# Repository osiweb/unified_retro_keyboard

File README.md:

## Unified Retrocomputer Keyboard Project

This project aims to provide a unified collection of keyboards and encoders for
vintage computers, with modular design to reuse as many elements as possible
across the designs.

Home computers of the 1970's typically either polled a switch matrix, or
interfaced to a parallel ASCII keyboard via a parallel port.

The keyboard allows use of Cherry MX keys, or Futaba MD-4PCS (aka George Risk
KBM-01-01) keys.

The keyboard is designed using KiCad in order to be the most useful for anybody
wishing to modify the keyboard for more specific uses, or to add to the project.

For construction and notes, see the the wiki at https://github.com/osiweb/unified_retro_keyboard/wiki.

### Capabilities so far:
- Replacement keyboard for OSI computers
- Replacement keyboard for Apple II/II+ computers
- Replacement keyboard for the Sol-20 computer
- Generic ADM-3A/Teletype style keyboard
- Apple I keyboard (multiple styles)
- Franklin ACE 1000 replacement keyboard by Chris Ryu (https://github.com/ryucats/Franklin-ACE-1000-Keyboard)

### Coming soon:
- Replace encoder board on Apple II/II+ keyboards
- Convert an OSI 542 keyboard into a generic ASCII keyboard
- Replica for Knight keyboard

### This keyboard project so far consists of:
- A classic retro-style ASCII keyboard, modeled after the ADM-3A keyboard, which
  can be also be populated to fit perfectly in an Apple II/II+ case (with corresponding Apple II keymaps), or an OSI
  case (with OSI adapter).
- A Sol-20 compatible keyboard.
- Keyscan/decoder interface modules that can output parallel ASCII, and can be adapted for other protocols.
- An OSI interface module, to connect the classic keyboard to an OSI computer.

### Firmware

The ASDF keyscan/encoder firmware lives in its own repository:
<https://github.com/unified-retro-keyboard/asdf-firmware>

- **Download page**: <https://unified-retro-keyboard.github.io/asdf-firmware/> — per-target `.hex` files and release notes.
- **GitHub Releases**: <https://github.com/unified-retro-keyboard/asdf-firmware/releases/latest>

The full firmware history, including everything that was previously under `firmware/`
in this repository, is preserved there.

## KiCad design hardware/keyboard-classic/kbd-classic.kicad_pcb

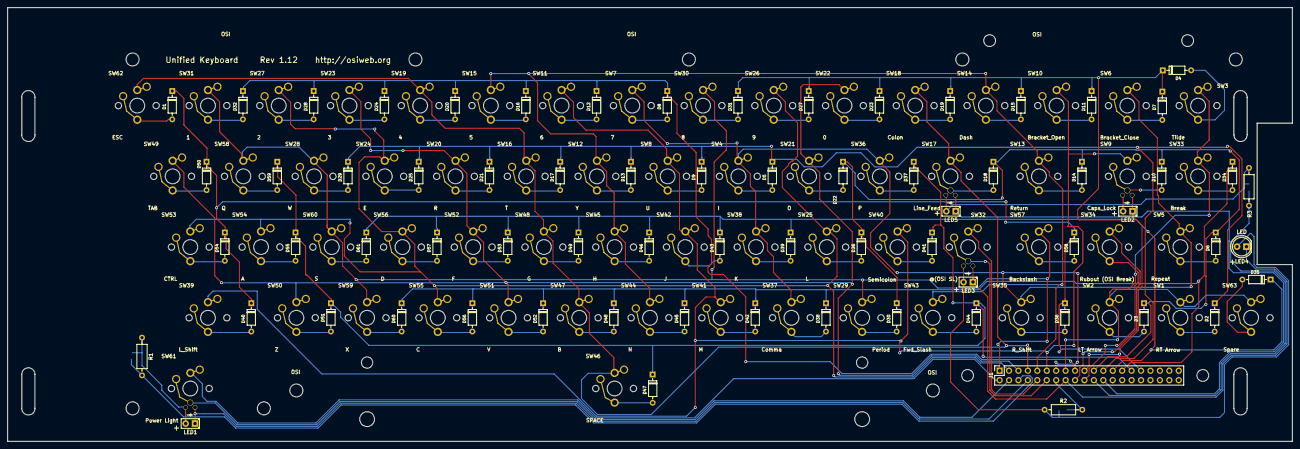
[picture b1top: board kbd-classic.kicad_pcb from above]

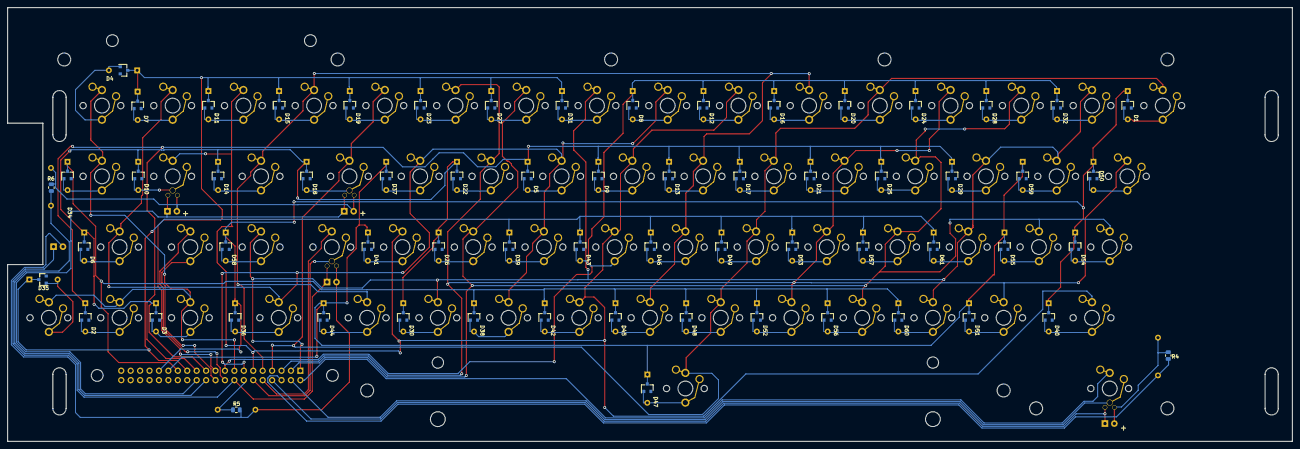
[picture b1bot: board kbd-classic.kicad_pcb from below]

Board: 2 copper layers, 346.1 x 116.8 mm, 135 parts (63 on the bottom side), 91 nets.

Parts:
D1, D2, D3, D4, D5, D6, D7, D8, D9, D10, D11, D12, D13, D14, D15, D16, D17, D18, D19, D20, D21, D22, D23, D24, D25, D26, D27, D28, D29, D30, D31, D32, D34, D35, D36, D37, D38, D39, D40, D41, D42, D43, D44, D45, D46, D47, D48, D49, D50, D51, D52, D53, D54, D55, D56, D57, D58, D59, D60, D61: 1N4148; diode-combined
J1: Controller; kbd_header_and_mounting_holes
LED1, LED2, LED3, LED5: LED; LED_D2.0mm_W4.8mm_H2.5mm_FlatTop
LED4: LED; LED_D5.0mm
R1, R2, R3: 470; R_Axial_DIN0207_L6.3mm_D2.5mm_P10.16mm_Horizontal
R4, R5, R6: 470; R_0805_2012Metric
SW1: RT Arrow; Key_MX
SW2: LT Arrow; Key_MX
SW3: Tilde; Key_MX
SW4: I; Key_MX
SW5: Repeat; Key_MX
SW6: Bracket_Close; Key_MX
SW7: 7; Key_MX
SW8: U; Key_MX
SW9: Caps_Lock; Key_MX_LED
SW10: Bracket_Open; Key_MX
SW11: 6; Key_MX
SW12: Y; Key_MX
SW13: Return; Key_MX
SW14: Dash; Key_MX
SW15: 5; Key_MX
SW16: T; Key_MX
SW17: Line_Feed; Key_MX_LED
SW18: Colon; Key_MX
SW19: 4; Key_MX
SW20: R; Key_MX
SW21: O; Key_MX
SW22: 0; Key_MX
SW23: 3; Key_MX
SW24: E; Key_MX
SW25: L; Key_MX
SW26: 9; Key_MX
SW27: 2; Key_MX
SW28: W; Key_MX
SW29: Period; Key_MX
SW30: 8; Key_MX
SW31: 1; Key_MX
SW32: @(OSI SL); Key_MX_LED
SW33: Break; Key_MX
SW34: Rubout (OSI Break); Key_MX
SW35: R_Shift; Key_MX
SW36: P; Key_MX
SW37: Comma; Key_MX
SW38: K; Key_MX
SW39: L_Shift; Key_MX
SW40: Semicolon; Key_MX
SW41: M; Key_MX
SW42: J; Key_MX
SW43: Fwd_Slash; Key_MX
SW44: N; Key_MX
SW45: H; Key_MX
SW46: SPACE; Key_MX_Spacebar_5.25
SW47: B; Key_MX
SW48: G; Key_MX
SW49: TAB; Key_MX
SW50: Z; Key_MX
SW51: V; Key_MX
SW52: F; Key_MX
SW53: CTRL; Key_MX
SW54: A; Key_MX
SW55: C; Key_MX
SW56: D; Key_MX
SW57: Backslash; Key_MX
SW58: Q; Key_MX
SW59: X; Key_MX
SW60: S; Key_MX
SW61: Power Light; Key_MX_LED
SW62: ESC; Key_MX
SW63: Spare; Key_MX

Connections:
/Col0: J1.15, SW1.1, SW2.1, SW3.1, SW33.1, SW63.1
/Col1: J1.13, SW4.1, SW5.1, SW6.1, SW7.1, SW35.1, SW36.1, SW37.1, SW38.1
/Col2: J1.11, SW8.1, SW9.1, SW10.1, SW11.1, SW39.1, SW40.1, SW41.1, SW42.1
/Col3: J1.9, SW12.1, SW13.1, SW14.1, SW15.1, SW43.1, SW44.1, SW45.1
/Col4: J1.7, SW16.1, SW17.1, SW18.1, SW19.1, SW46.1, SW47.1, SW48.1, SW62.1
/Col5: J1.5, SW20.1, SW21.1, SW22.1, SW23.1, SW49.1, SW50.1, SW51.1, SW52.1
/Col6: J1.3, SW24.1, SW25.1, SW26.1, SW27.1, SW53.1, SW54.1, SW55.1, SW56.1
/Col7: J1.1, SW28.1, SW29.1, SW30.1, SW31.1, SW57.1, SW58.1, SW59.1, SW60.1
/Row0: D1.1 (K), D36.1 (K), D40.1 (K), D50.1 (K), D54.1 (K), D58.1 (K), J1.31
/Row1: D37.1 (K), D41.1 (K), D44.1 (K), D47.1 (K), D51.1 (K), D55.1 (K), D59.1 (K), J1.29
/Row2: D34.1 (K), D38.1 (K), D42.1 (K), D45.1 (K), D48.1 (K), D52.1 (K), D56.1 (K), D60.1 (K), J1.27
/Row3: D35.1 (K), D39.1 (K), D43.1 (K), D46.1 (K), D49.1 (K), D53.1 (K), D57.1 (K), D61.1 (K), J1.25
/Row4: D2.1 (K), D5.1 (K), D9.1 (K), D13.1 (K), D17.1 (K), D21.1 (K), D25.1 (K), D29.1 (K), J1.23
/Row5: D3.1 (K), D6.1 (K), D10.1 (K), D14.1 (K), D18.1 (K), D22.1 (K), D26.1 (K), D30.1 (K), J1.21
/Row6: D4.1 (K), D7.1 (K), D11.1 (K), D15.1 (K), D19.1 (K), D23.1 (K), D27.1 (K), D31.1 (K), J1.19
/Row7: D8.1 (K), D12.1 (K), D16.1 (K), D20.1 (K), D24.1 (K), D28.1 (K), D32.1 (K), J1.17
unnamed: D1.2 (A), SW62.2
unnamed: D2.2 (A), SW1.2
unnamed: D3.2 (A), SW2.2
unnamed: D4.2 (A), SW3.2
unnamed: D5.2 (A), SW4.2
unnamed: D6.2 (A), SW5.2
unnamed: D7.2 (A), SW6.2
unnamed: D8.2 (A), SW7.2
unnamed: D9.2 (A), SW8.2
unnamed: D10.2 (A), SW9.2
unnamed: D11.2 (A), SW10.2
unnamed: D12.2 (A), SW11.2
unnamed: D13.2 (A), SW12.2
unnamed: D14.2 (A), SW13.2
unnamed: D15.2 (A), SW14.2
unnamed: D16.2 (A), SW15.2
unnamed: D17.2 (A), SW16.2
unnamed: D18.2 (A), SW17.2
unnamed: D19.2 (A), SW18.2
unnamed: D20.2 (A), SW19.2
unnamed: D21.2 (A), SW20.2
unnamed: D22.2 (A), SW21.2
unnamed: D23.2 (A), SW22.2
unnamed: D24.2 (A), SW23.2
unnamed: D25.2 (A), SW24.2
unnamed: D26.2 (A), SW25.2
unnamed: D27.2 (A), SW26.2
unnamed: D28.2 (A), SW27.2
unnamed: D29.2 (A), SW28.2
unnamed: D30.2 (A), SW29.2
unnamed: D31.2 (A), SW30.2
unnamed: D32.2 (A), SW31.2
unnamed: D34.2 (A), SW33.2
unnamed: D35.2 (A), SW63.2
unnamed: D36.2 (A), SW35.2
unnamed: D37.2 (A), SW36.2
unnamed: D38.2 (A), SW37.2
unnamed: D39.2 (A), SW38.2
unnamed: D40.2 (A), SW39.2
unnamed: D41.2 (A), SW40.2
unnamed: D42.2 (A), SW41.2
unnamed: D43.2 (A), SW42.2
unnamed: D44.2 (A), SW43.2
unnamed: D45.2 (A), SW44.2
unnamed: D46.2 (A), SW45.2
unnamed: D47.2 (A), SW46.2
unnamed: D48.2 (A), SW47.2
unnamed: D49.2 (A), SW48.2
unnamed: D50.2 (A), SW49.2
unnamed: D51.2 (A), SW50.2
unnamed: D52.2 (A), SW51.2
unnamed: D53.2 (A), SW52.2
unnamed: D54.2 (A), SW53.2
unnamed: D55.2 (A), SW54.2
unnamed: D56.2 (A), SW55.2
unnamed: D57.2 (A), SW56.2
unnamed: D58.2 (A), SW57.2
unnamed: D59.2 (A), SW58.2
unnamed: D60.2 (A), SW59.2
unnamed: D61.2 (A), SW60.2
unnamed: J1.2, SW61.1
unnamed: J1.4, SW61.2
unnamed: J1.6, R1.2, R4.2
unnamed: J1.8, LED1.1 (K), SW61.4
unnamed: J1.10, SW32.1
unnamed: J1.12, SW32.2
unnamed: J1.14, R2.2, R5.2
unnamed: J1.16, LED3.1 (K), LED4.1 (K), SW32.4
unnamed: J1.18, SW34.1
unnamed: J1.20, SW34.2
unnamed: J1.22, R3.1, R6.1
unnamed: J1.24, LED2.1 (K), LED5.1 (K), SW9.4, SW17.4
unnamed: LED1.2 (A), R1.1, R4.1, SW61.3
unnamed: LED2.2 (A), LED5.2 (A), R3.2, R6.2, SW9.3, SW17.3
unnamed: LED3.2 (A), LED4.2 (A), R2.1, R5.1, SW32.3

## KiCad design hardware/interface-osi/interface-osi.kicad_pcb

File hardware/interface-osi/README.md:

* OSI Compatible interface

An interface for OSI computers that is compatible with the OSI 542C keyboard, including sound circuits.  

This interface also permits substitution of a soft-shiftlock function using 
a regular momentary keyswitch, instead of the hard-to-fine latchine keyswitch.
An LED is provided to indicate SHIFT LOCK status.  This interface mates with
the Classic ASCII keyboard, configured with the OSI keycaps.  

**Construction Notes:

1. If a diode per key is installed on the keyboard, then omit diodes D1-D8 and install D18.

1. If the keyboard is not installed with a diode per key, then install D1-D8, and omit D18.

1. The RESET delay is about 3 seconds with a 6.8 uF capacitor at C20.  4.7 uF gives about
2 seconds, and 3.3 uF gives about a 1 second delay.

1. If you want to use the sound circuit with an older 540A video board, then on the 540A board, jumper pin 13
of IC E4 to pin 15 of the keyboard connector, and on the OSI interface board, set JP1 to "S1".

1. If you use a 540B video board, then set JP1 to "/S1"

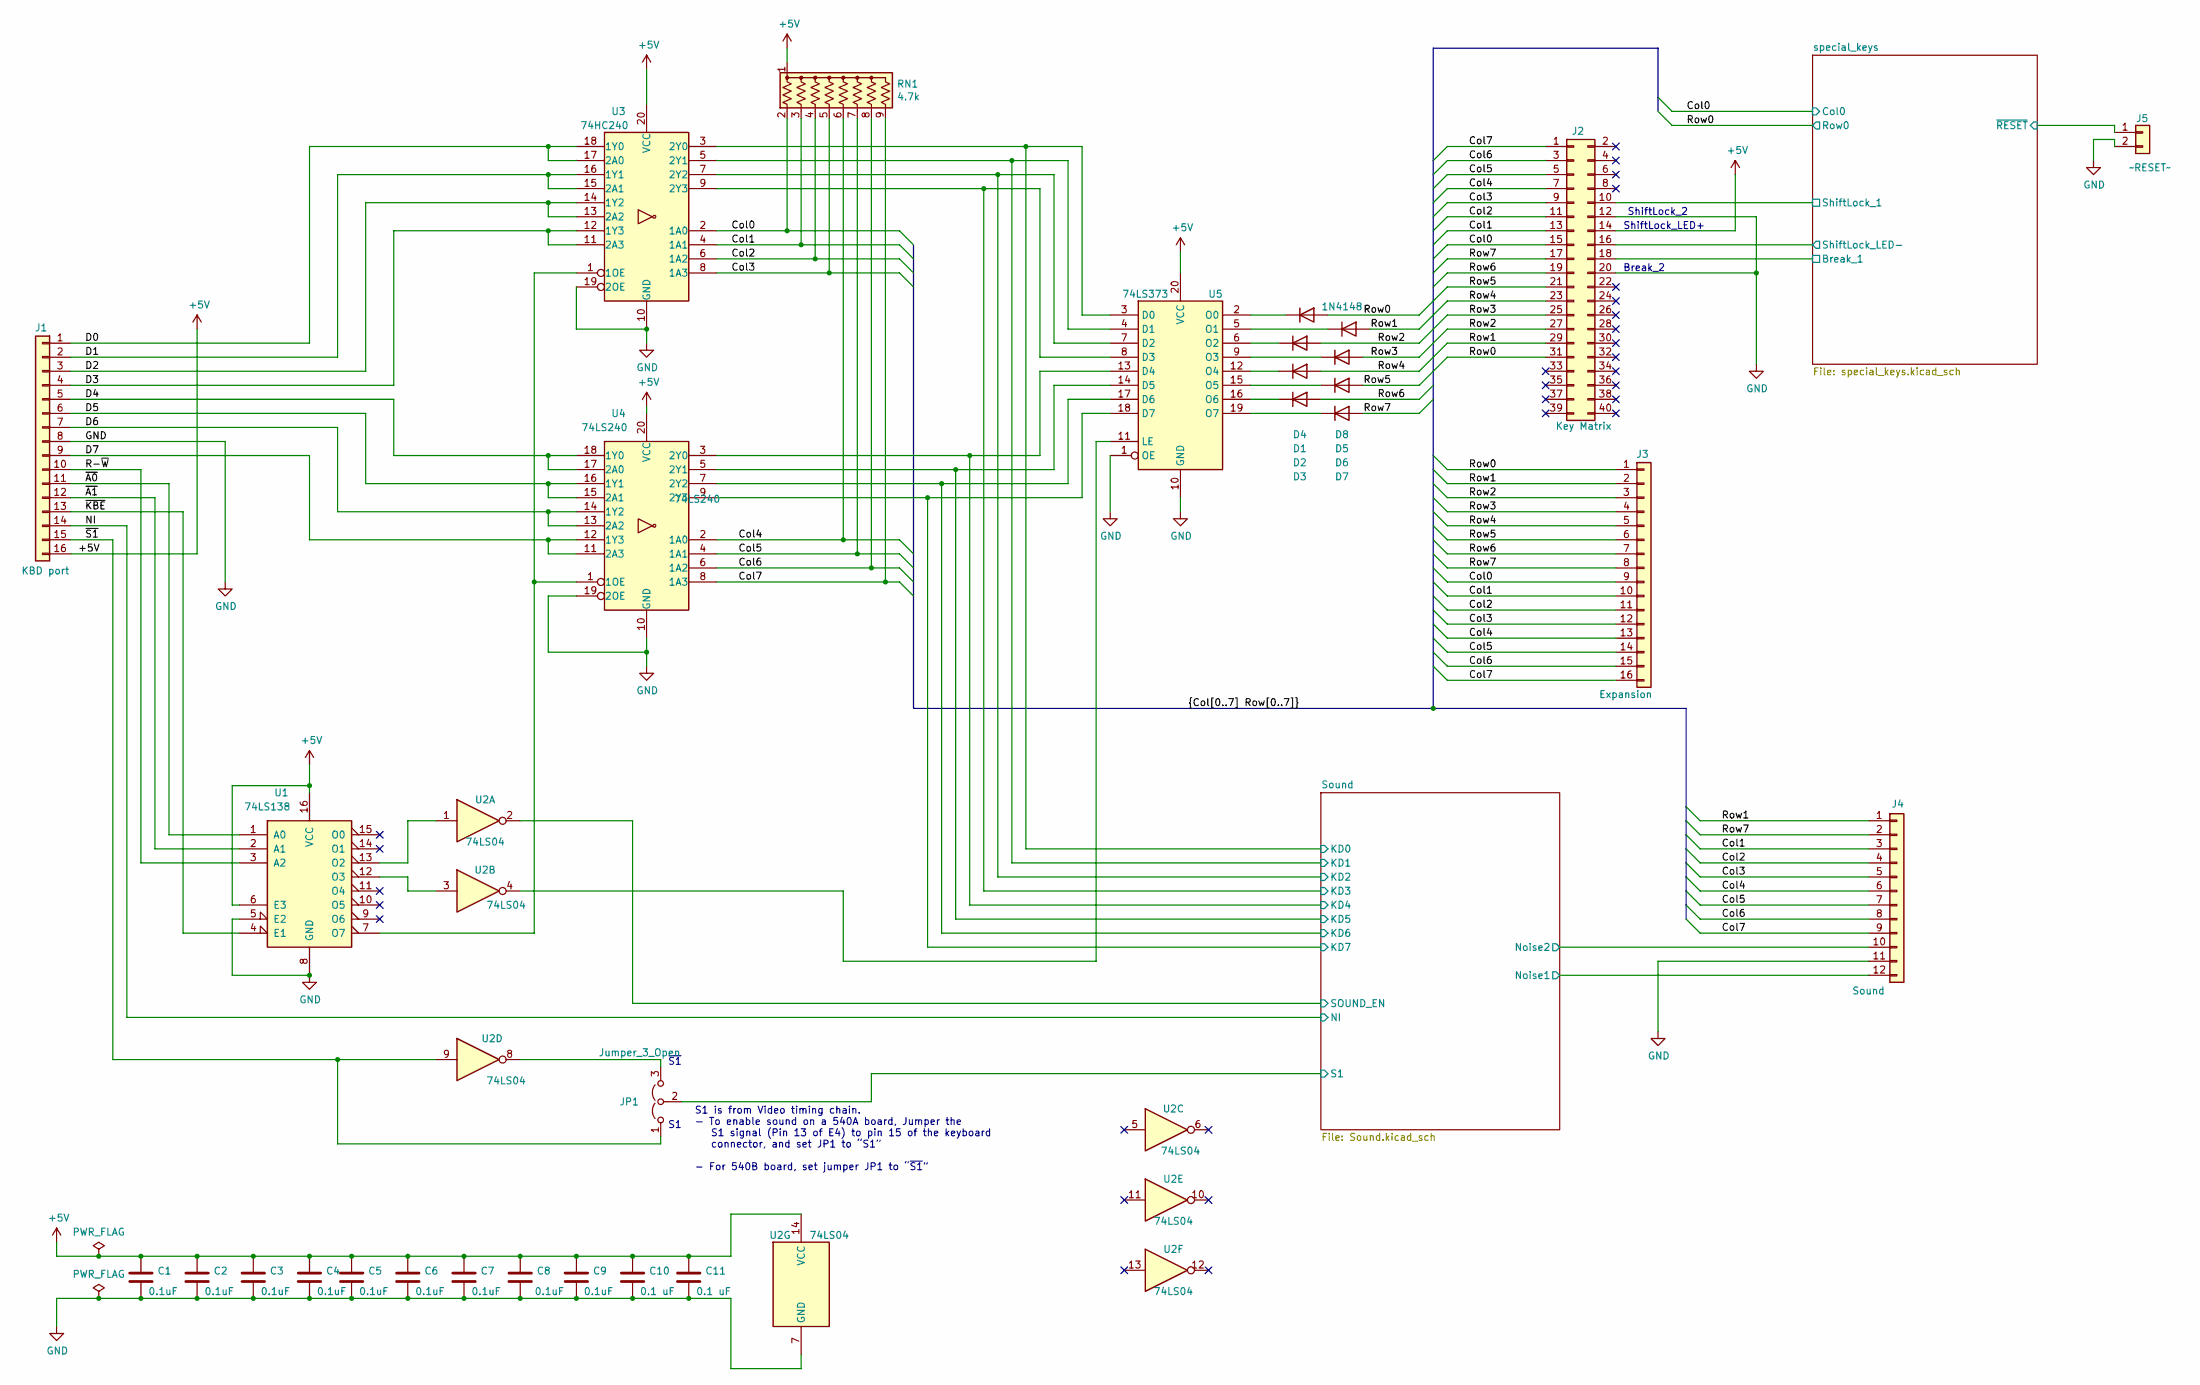
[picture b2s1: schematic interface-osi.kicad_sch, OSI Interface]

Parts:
C1, C2, C3, C4, C5, C6, C7, C8, C9: 0.1uF; C_Disc_D3.0mm_W2.0mm_P2.50mm
C10, C11: 0.1 uF; C_Disc_D3.0mm_W2.0mm_P2.50mm
D1, D2, D3, D4, D5, D6, D7, D8: 1N4148; D_DO-35_SOD27_P7.62mm_Horizontal_bypassed
J1: KBD port; DIP-16_W7.62mm_Socket
J2: Key Matrix; kbd_header_and_mounting_holes
J3: Expansion; DIP-16_W7.62mm_Socket
J4: Sound; Molex_KK-396_A-41791-0012_1x12_P3.96mm_Vertical
J5: ~RESET~; Molex_KK-396_A-41791-0002_1x02_P3.96mm_Vertical
JP1: Jumper_3_Open; PinHeader_1x03_P2.54mm_Horizontal
RN1: 4.7k; R_Array_SIP9
U1: 74LS138; DIP-16_W7.62mm
U2: 74LS04; DIP-14_W7.62mm
U3: 74HC240; DIP-20_W7.62mm; Tolerance n/a; Power Rating If applicable; Manufacturer PN SN74LS240N
U4: 74LS240; DIP-20_W7.62mm; Tolerance n/a; Power Rating If applicable; Manufacturer PN SN74LS240N
U5: 74LS373; DIP-20_W7.62mm

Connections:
+5V: C1.1, C2.1, C3.1, C4.1, C5.1, C6.1, C7.1, C8.1, C9.1, C10.1, C11.1, J1.16, J2.14, RN1.1 (common), U1.6 (E3), U1.16 (VCC), U2.14 (VCC), U3.20 (VCC), U4.20 (VCC), U5.20 (VCC); also elsewhere on the board
/Col0: J2.15, J3.9, RN1.2 (R1), U3.2 (1A0); also elsewhere on the board
/Col1: J2.13, J3.10, J4.3, RN1.3 (R2), U3.4 (1A1)
/Col2: J2.11, J3.11, J4.4, RN1.4 (R3), U3.6 (1A2)
/Col3: J2.9, J3.12, J4.5, RN1.5 (R4), U3.8 (1A3)
/Col4: J2.7, J3.13, J4.6, RN1.6 (R5), U4.2 (1A0)
/Col5: J2.5, J3.14, J4.7, RN1.7 (R6), U4.4 (1A1)
/Col6: J2.3, J3.15, J4.8, RN1.8 (R7), U4.6 (1A2)
/Col7: J2.1, J3.16, J4.9, RN1.9 (R8), U4.8 (1A3)
/D0: J1.1, U3.17 (2A0), U3.18 (1Y0)
/D1: J1.2, U3.15 (2A1), U3.16 (1Y1)
/D2: J1.3, U3.13 (2A2), U3.14 (1Y2)
/D3: J1.4, U3.11 (2A3), U3.12 (1Y3)
/D4: J1.5, U4.17 (2A0), U4.18 (1Y0)
/D5: J1.6, U4.15 (2A1), U4.16 (1Y1)
/D6: J1.7, U4.13 (2A2), U4.14 (1Y2)
/D7: J1.9, U4.11 (2A3), U4.12 (1Y3)
/NI: J1.14; also elsewhere on the board
/R-~W: J1.10, U1.3 (A2)
/Row0: D4.2 (A), J2.31, J3.1; also elsewhere on the board
/Row1: D8.2 (A), J2.29, J3.2, J4.1
/Row2: D1.2 (A), J2.27, J3.3
/Row3: D5.2 (A), J2.25, J3.4
/Row4: D2.2 (A), J2.23, J3.5
/Row5: D6.2 (A), J2.21, J3.6
/Row6: D3.2 (A), J2.19, J3.7
/Row7: D7.2 (A), J2.17, J3.8, J4.2
/Sound/KD0: U3.3 (2Y0), U5.3 (D0); also elsewhere on the board
/Sound/KD1: U3.5 (2Y1), U5.4 (D1); also elsewhere on the board
/Sound/KD2: U3.7 (2Y2), U5.7 (D2); also elsewhere on the board
/Sound/KD3: U3.9 (2Y3), U5.8 (D3); also elsewhere on the board
/Sound/KD4: U4.3 (2Y0), U5.13 (D4); also elsewhere on the board
/Sound/KD5: U4.5 (2Y1), U5.14 (D5); also elsewhere on the board
/Sound/KD6: U4.7 (2Y2), U5.17 (D6); also elsewhere on the board
/Sound/KD7: U4.9 (2Y3), U5.18 (D7); also elsewhere on the board
/Sound/Noise1: J4.12; also elsewhere on the board
/Sound/S1: JP1.2 (C); also elsewhere on the board
/Sound/SOUND_EN: U2.2; also elsewhere on the board
/special_keys/Break_1: J2.18; also elsewhere on the board
/special_keys/ShiftLock_1: J2.10; also elsewhere on the board
/special_keys/ShiftLock_LED-: J2.16; also elsewhere on the board
/special_keys/~RESET: J5.1; also elsewhere on the board
/~A0: J1.11, U1.1 (A0)
/~A1: J1.12, U1.2 (A1)
/~KBE: J1.13, U1.4 (E1)
/~S1: J1.15, JP1.1 (A), U2.9
GND: C1.2, C2.2, C3.2, C4.2, C5.2, C6.2, C7.2, C8.2, C9.2, C10.2, C11.2, J1.8, J2.12, J2.20, J4.11, J5.2, U1.5 (E2), U1.8 (GND), U2.7 (GND), U3.10 (GND), U3.19 (2OE), U4.10 (GND), U4.19 (2OE), U5.1 (OE), U5.10 (GND); also elsewhere on the board
unnamed: D1.1 (K), U5.6 (O2)
unnamed: D2.1 (K), U5.12 (O4)
unnamed: D3.1 (K), U5.16 (O6)
unnamed: D4.1 (K), U5.2 (O0)
unnamed: D5.1 (K), U5.9 (O3)
unnamed: D6.1 (K), U5.15 (O5)
unnamed: D7.1 (K), U5.19 (O7)
unnamed: D8.1 (K), U5.5 (O1)
unnamed: JP1.3 (B), U2.8
unnamed: U1.13 (O2), U2.1
unnamed: U1.12 (O3), U2.3
unnamed: U1.7 (O7), U3.1 (1OE), U4.1 (1OE)
unnamed: U2.4, U5.11 (LE)

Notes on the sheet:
ShiftLock_2
ShiftLock_LED+
S1 is from Video timing chain. - To enable sound on a 540A board, Jumper the S1 signal (Pin 13 of E4) to pin 15 of the keyboard connector, and set JP1 to “S1” - For 540B board, set jumper JP1 to “~{S1}”
Break_2
~{S1}

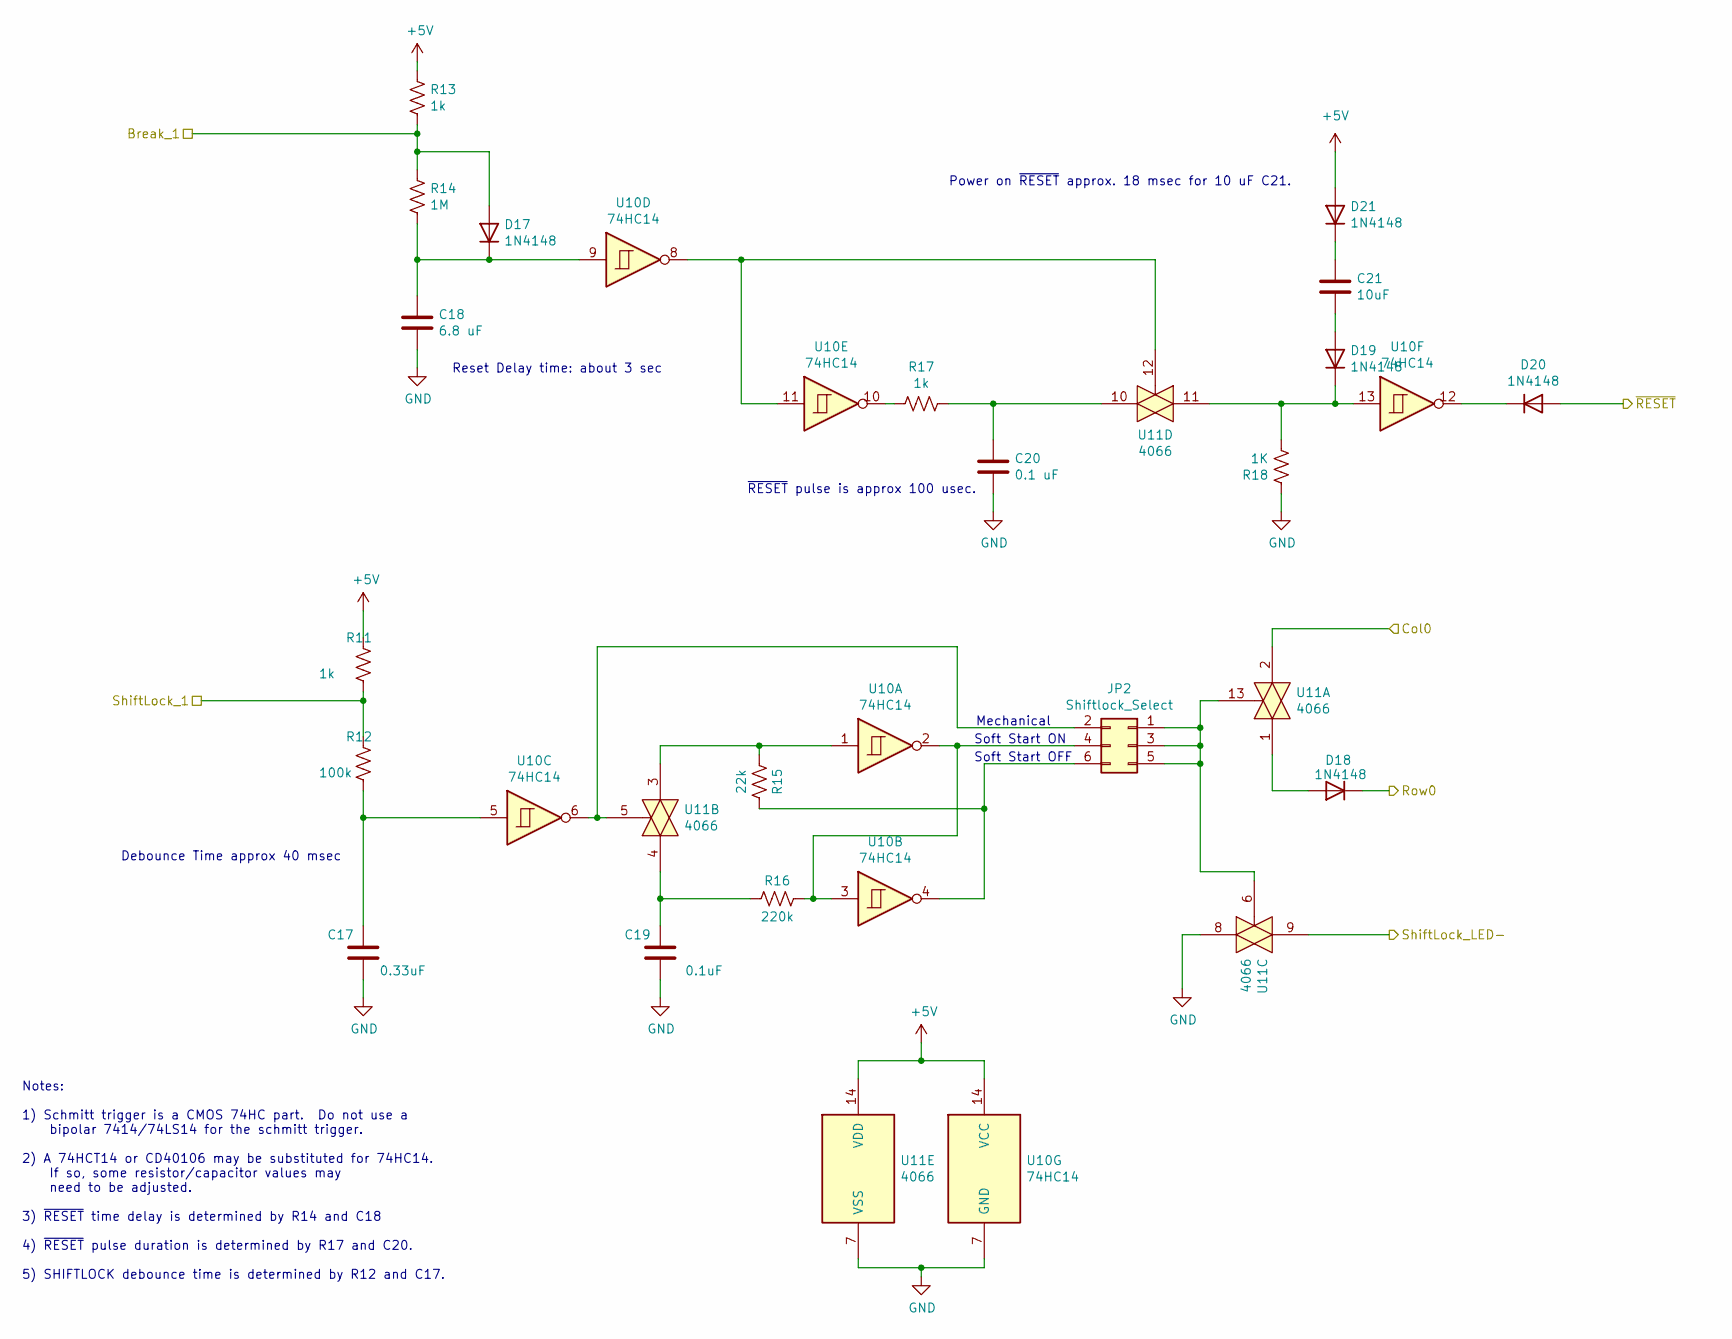
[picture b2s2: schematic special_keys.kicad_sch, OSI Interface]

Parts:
C17: 0.33uF; C_Disc_D3.0mm_W2.0mm_P2.50mm
C18: 6.8 uF; C_Disc_D3.0mm_W2.0mm_P2.50mm
C19: 0.1uF; C_Disc_D3.0mm_W2.0mm_P2.50mm
C20: 0.1 uF; C_Disc_D3.0mm_W2.0mm_P2.50mm
C21: 10uF; C_Disc_D3.0mm_W2.0mm_P2.50mm
D17, D18, D19, D20, D21: 1N4148; D_DO-35_SOD27_P7.62mm_Horizontal
JP2: Shiftlock_Select; PinHeader_2x03_P2.54mm_Horizontal
R11, R13, R17: 1k; R_Axial_DIN0207_L6.3mm_D2.5mm_P10.16mm_Horizontal
R12: 100k; R_Axial_DIN0207_L6.3mm_D2.5mm_P10.16mm_Horizontal
R14: 1M; R_Axial_DIN0207_L6.3mm_D2.5mm_P10.16mm_Horizontal
R15: 22k; R_Axial_DIN0207_L6.3mm_D2.5mm_P10.16mm_Horizontal
R16: 220k; R_Axial_DIN0207_L6.3mm_D2.5mm_P10.16mm_Horizontal
R18: 1K; R_Axial_DIN0207_L6.3mm_D2.5mm_P10.16mm_Horizontal
U10: 74HC14; DIP-14_W7.62mm
U11: 4066; DIP-14_W7.62mm

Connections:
+5V: D21.2 (A), R11.1, R13.1, U10.14 (VCC), U11.14 (VDD); also elsewhere on the board
/Col0: U11.2; also elsewhere on the board
/Row0: D18.1 (K); also elsewhere on the board
/special_keys/Break_1: D17.2 (A), R13.2, R14.1; also elsewhere on the board
/special_keys/ShiftLock_1: R11.2, R12.1; also elsewhere on the board
/special_keys/ShiftLock_LED-: U11.9; also elsewhere on the board
/special_keys/~RESET: D20.2 (A); also elsewhere on the board
GND: C17.1, C18.2, C19.1, C20.2, R18.1, U10.7 (GND), U11.7 (VSS), U11.8; also elsewhere on the board
unnamed: C17.2, R12.2, U10.5
unnamed: C19.2, R16.1, U11.4
unnamed: C20.1, R17.1, U11.10
unnamed: C18.1, D17.1 (K), R14.2, U10.9
unnamed: D18.2 (A), U11.1
unnamed: C21.2, D19.2 (A)
unnamed: D19.1 (K), R18.2, U10.13, U11.11
unnamed: D20.1 (K), U10.12
unnamed: C21.1, D21.1 (K)
unnamed: JP2.1, JP2.3, JP2.5, U11.6, U11.13
unnamed: JP2.2, U10.6, U11.5
unnamed: JP2.4, R16.2, U10.2, U10.3
unnamed: JP2.6, R15.2, U10.4
unnamed: R15.1, U10.1, U11.3
unnamed: R17.2, U10.10
unnamed: U10.8, U10.11, U11.12

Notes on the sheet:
Power on ~{RESET} approx. 18 msec for 10 uF C21.
Reset Delay time: about 3 sec
Debounce Time approx 40 msec
~{RESET} pulse is approx 100 usec.
Notes: 1) Schmitt trigger is a CMOS 74HC part. Do not use a bipolar 7414/74LS14 for the schmitt trigger. 2) A 74HCT14 or CD40106 may be substituted for 74HC14. If so, some resistor/capacitor values may need to be adjusted. 3) ~{RESET} time delay is determined by R14 and C18 4) ~{RESET} pulse durati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
Mechanical
Soft Start OFF
Soft Start ON

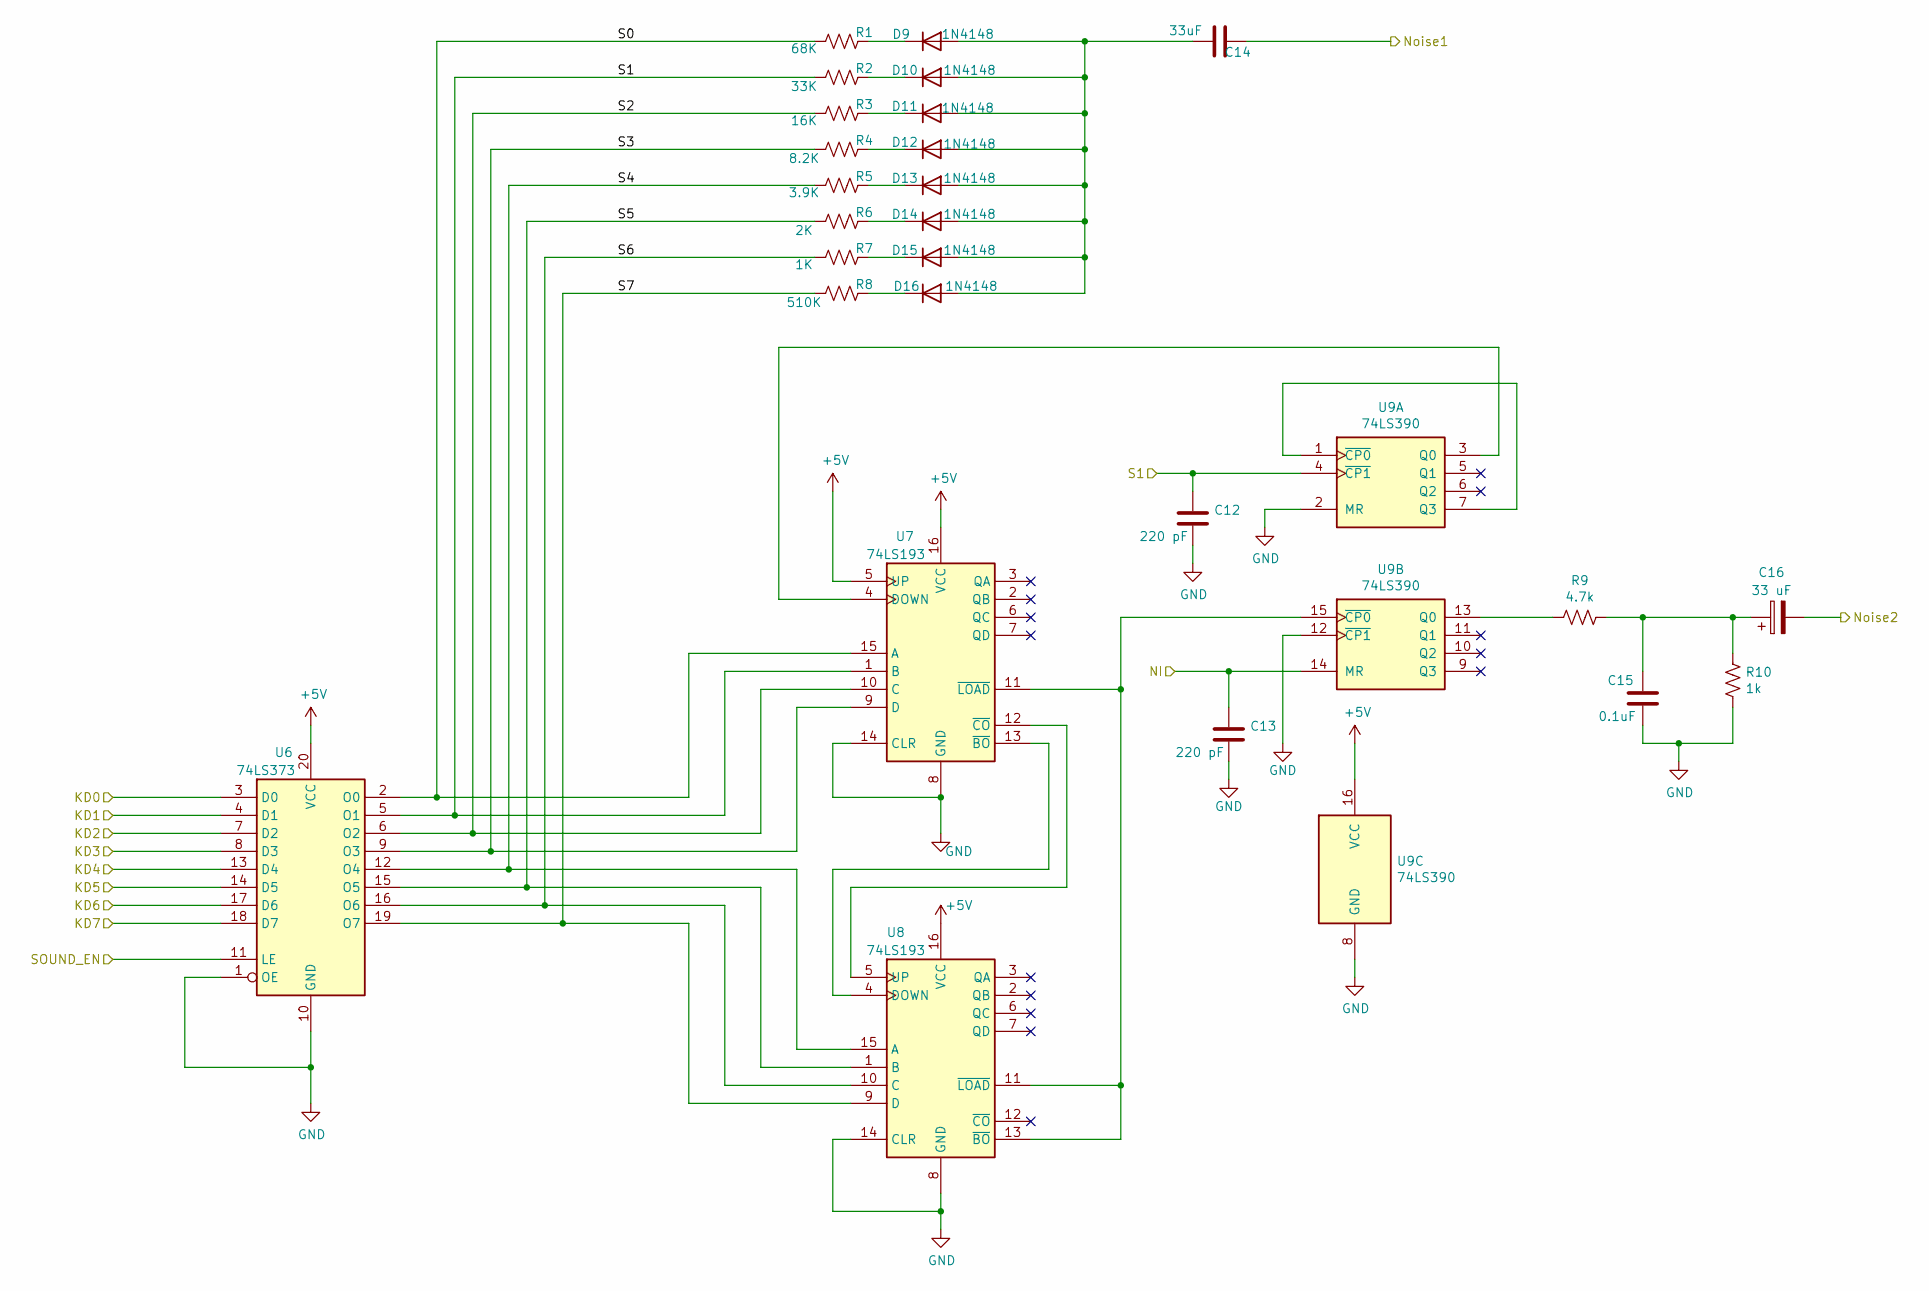
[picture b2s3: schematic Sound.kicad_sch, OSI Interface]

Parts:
C12, C13: 220 pF; C_Disc_D3.0mm_W2.0mm_P2.50mm
C14: 33uF; C_Disc_D3.0mm_W2.0mm_P2.50mm
C15: 0.1uF; C_Disc_D3.0mm_W2.0mm_P2.50mm
C16: 33 uF; CP_Radial_D4.0mm_P1.50mm
D9, D10, D11, D12, D13, D14, D15, D16: 1N4148; D_DO-35_SOD27_P7.62mm_Horizontal
R1: 68K; R_Axial_DIN0207_L6.3mm_D2.5mm_P10.16mm_Horizontal
R2: 33K; R_Axial_DIN0207_L6.3mm_D2.5mm_P10.16mm_Horizontal
R3: 16K; R_Axial_DIN0207_L6.3mm_D2.5mm_P10.16mm_Horizontal
R4: 8.2K; R_Axial_DIN0207_L6.3mm_D2.5mm_P10.16mm_Horizontal
R5: 3.9K; R_Axial_DIN0207_L6.3mm_D2.5mm_P10.16mm_Horizontal
R6: 2K; R_Axial_DIN0207_L6.3mm_D2.5mm_P10.16mm_Horizontal
R7: 1K; R_Axial_DIN0207_L6.3mm_D2.5mm_P10.16mm_Horizontal
R8: 510K; R_Axial_DIN0207_L6.3mm_D2.5mm_P10.16mm_Horizontal
R9: 4.7k; R_Axial_DIN0207_L6.3mm_D2.5mm_P10.16mm_Horizontal
R10: 1k; R_Axial_DIN0207_L6.3mm_D2.5mm_P10.16mm_Horizontal
U6: 74LS373; DIP-20_W7.62mm
U7, U8: 74LS193; DIP-16_W7.62mm
U9: 74LS390; DIP-16_W7.62mm

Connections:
+5V: U6.20 (VCC), U7.5 (UP), U7.16 (VCC), U8.16 (VCC), U9.16 (VCC); also elsewhere on the board
/NI: C13.1, U9.14 (MR); also elsewhere on the board
/Sound/KD0: U6.3 (D0); also elsewhere on the board
/Sound/KD1: U6.4 (D1); also elsewhere on the board
/Sound/KD2: U6.7 (D2); also elsewhere on the board
/Sound/KD3: U6.8 (D3); also elsewhere on the board
/Sound/KD4: U6.13 (D4); also elsewhere on the board
/Sound/KD5: U6.14 (D5); also elsewhere on the board
/Sound/KD6: U6.17 (D6); also elsewhere on the board
/Sound/KD7: U6.18 (D7); also elsewhere on the board
/Sound/Noise1: C14.1; also elsewhere on the board
/Sound/S0: R1.2, U6.2 (O0), U7.15 (A)
/Sound/S1: C12.1, R2.2, U6.5 (O1), U7.1 (B), U9.4 (~CP1); also elsewhere on the board
/Sound/S2: R3.2, U6.6 (O2), U7.10 (C)
/Sound/S3: R4.2, U6.9 (O3), U7.9 (D)
/Sound/S4: R5.2, U6.12 (O4), U8.15 (A)
/Sound/S5: R6.2, U6.15 (O5), U8.1 (B)
/Sound/S6: R7.2, U6.16 (O6), U8.10 (C)
/Sound/S7: R8.2, U6.19 (O7), U8.9 (D)
/Sound/SOUND_EN: U6.11 (LE); also elsewhere on the board
GND: C12.2, C13.2, C15.2, R10.2, U6.1 (OE), U6.10 (GND), U7.8 (GND), U7.14 (CLR), U8.8 (GND), U8.14 (CLR), U9.2 (MR), U9.8 (GND), U9.12 (~CP1); also elsewhere on the board
unnamed: D9.1 (K), R1.1
unnamed: C14.2, D9.2 (A), D10.2 (A), D11.2 (A), D12.2 (A), D13.2 (A), D14.2 (A), D15.2 (A), D16.2 (A)
unnamed: D10.1 (K), R2.1
unnamed: D11.1 (K), R3.1
unnamed: D12.1 (K), R4.1
unnamed: D13.1 (K), R5.1
unnamed: D14.1 (K), R6.1
unnamed: D15.1 (K), R7.1
unnamed: D16.1 (K), R8.1
unnamed: U7.4 (DOWN), U9.3 (Q0)
unnamed: U7.13 (~BO), U8.4 (DOWN)
unnamed: U7.12 (~CO), U8.5 (UP)
unnamed: U7.11 (~LOAD), U8.11 (~LOAD), U8.13 (~BO), U9.15 (~CP0)
unnamed: U9.1 (~CP0), U9.7 (Q3)
unnamed: R9.2, U9.13 (Q0)

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
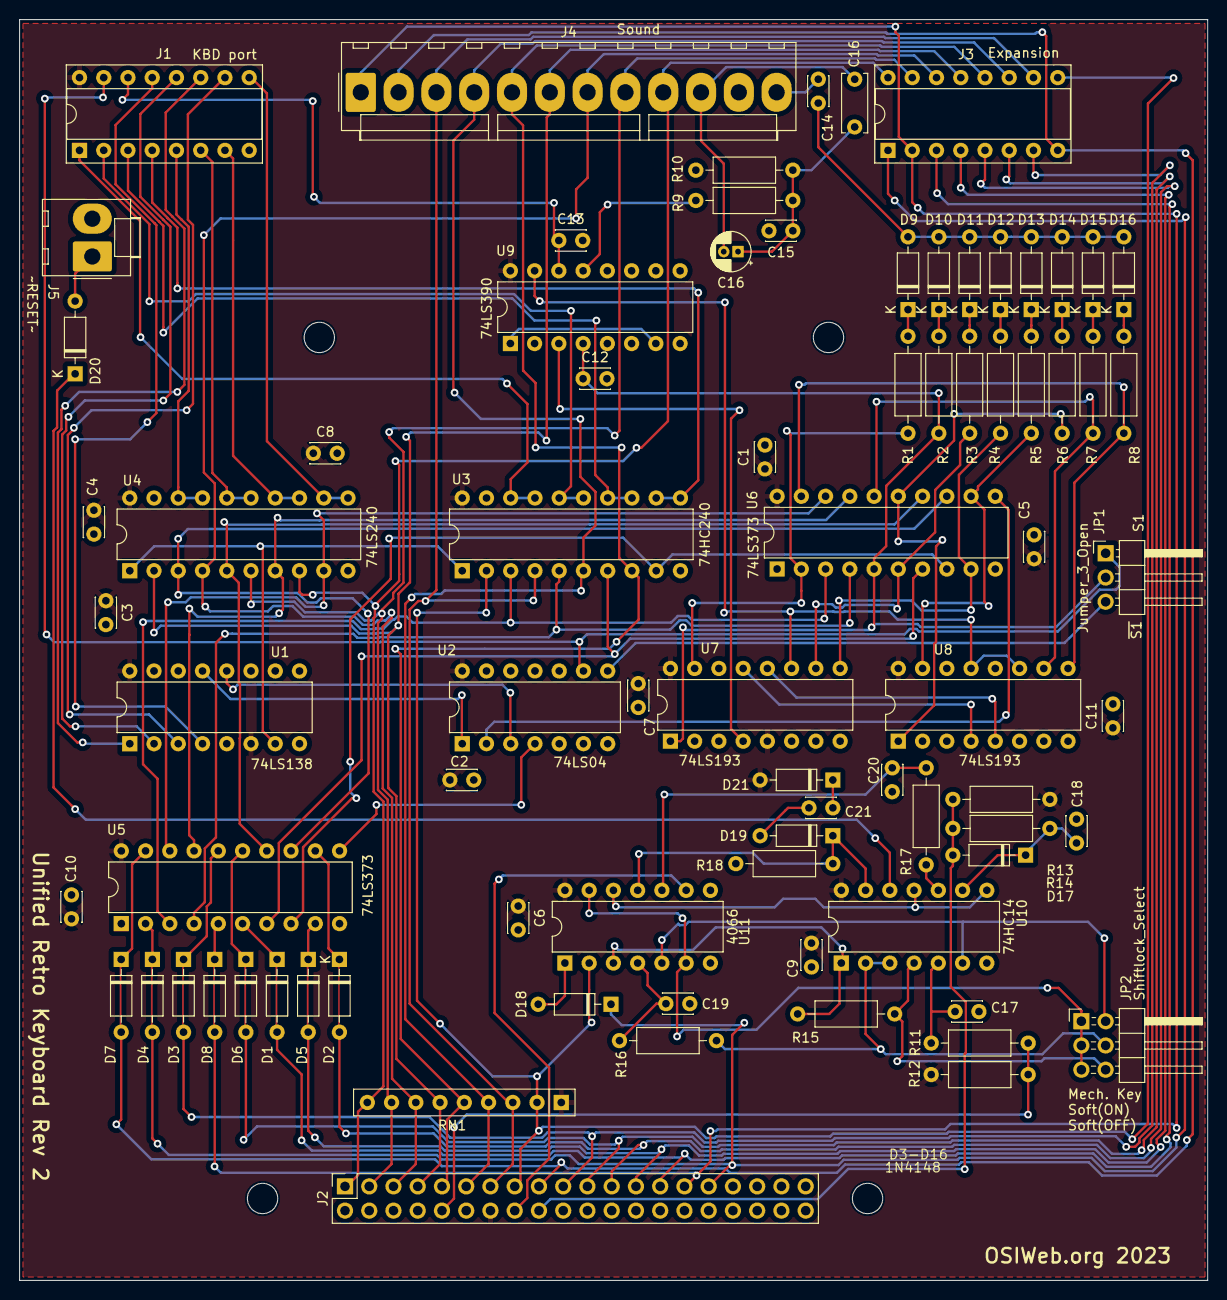
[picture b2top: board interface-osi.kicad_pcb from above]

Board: 2 copper layers, 124.5 x 132.1 mm, 80 parts (0 on the bottom side), 100 nets.

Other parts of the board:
C16#2: 33 uF; CP_Radial_D4.0mm_P1.50mm
